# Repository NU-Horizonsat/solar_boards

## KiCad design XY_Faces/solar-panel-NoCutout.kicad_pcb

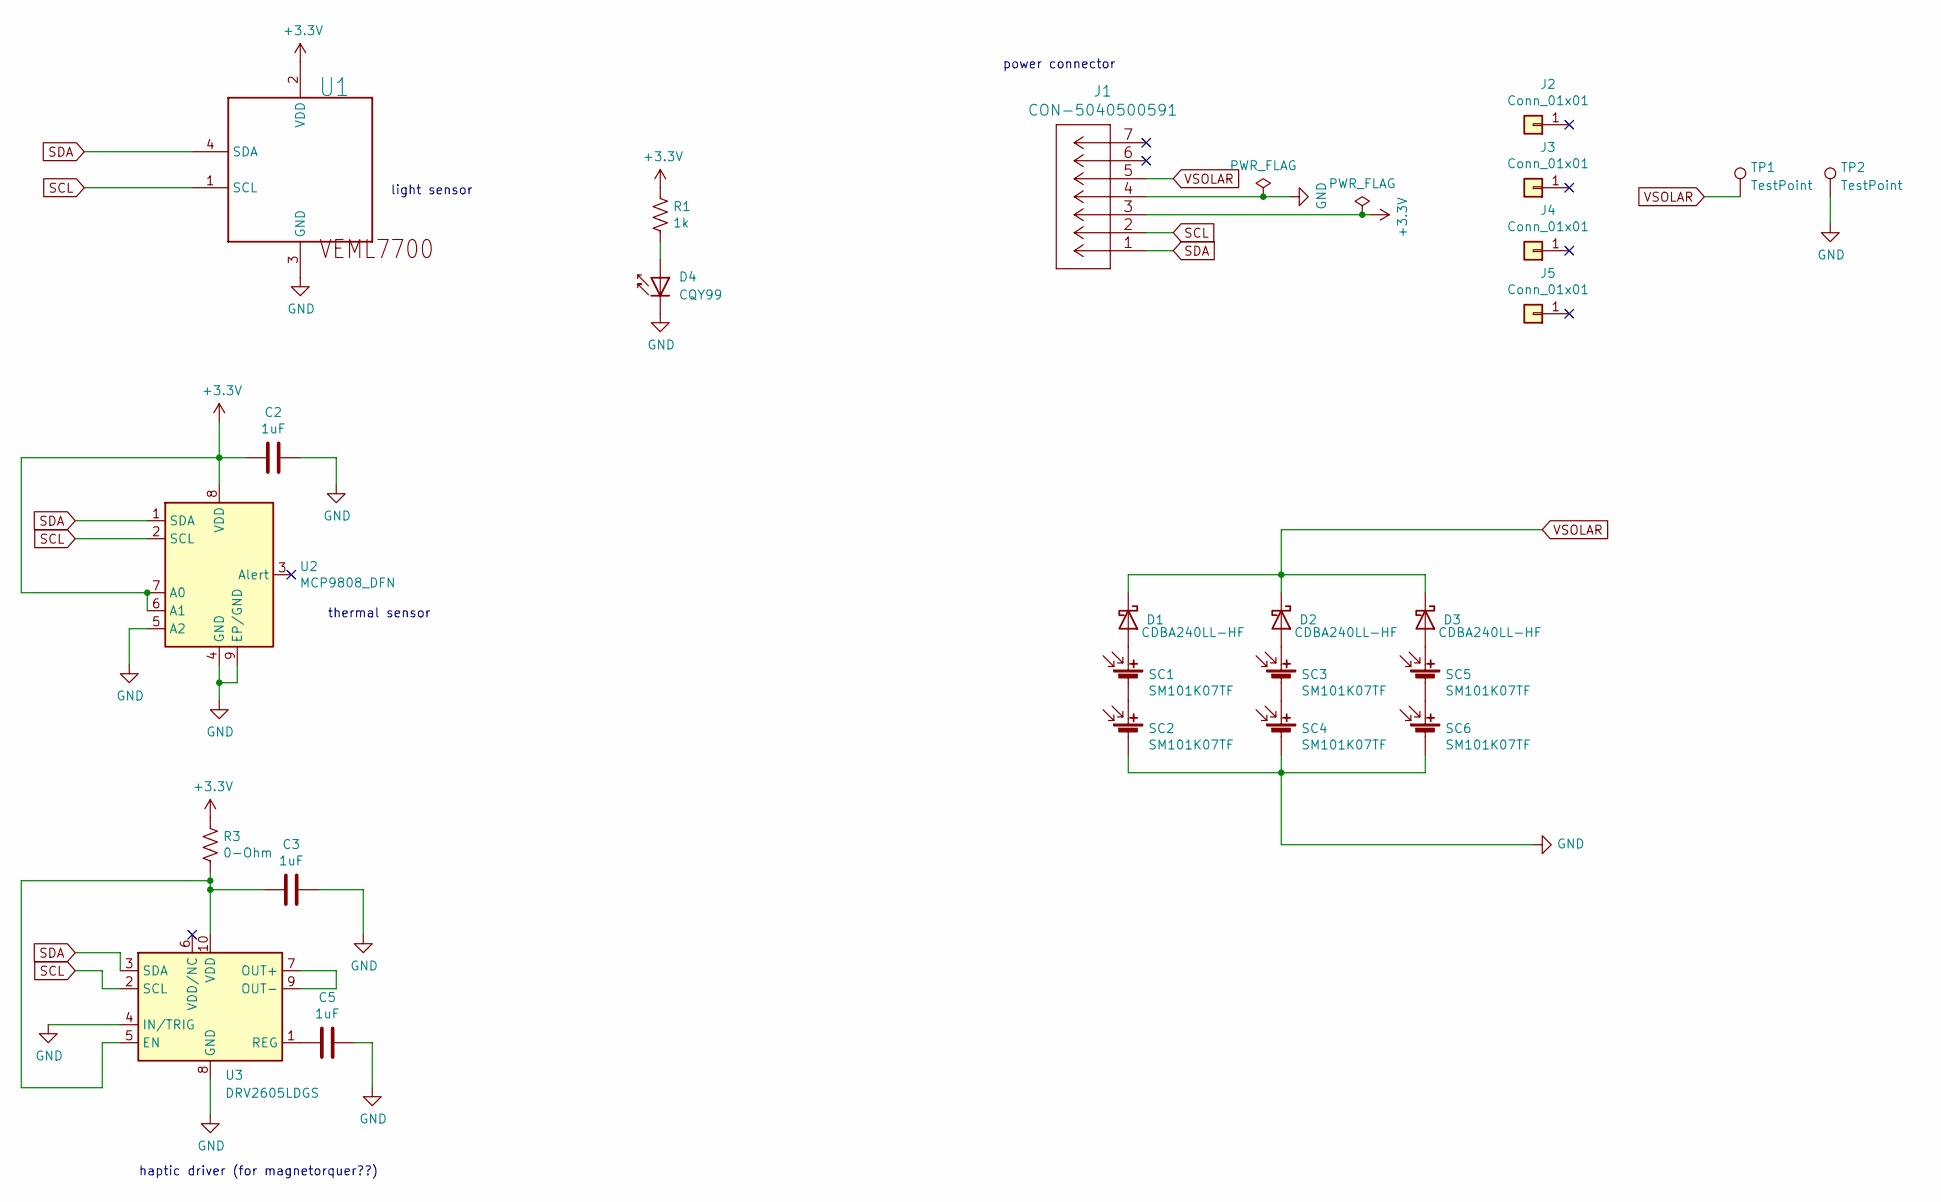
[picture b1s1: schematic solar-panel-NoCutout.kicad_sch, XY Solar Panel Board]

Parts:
C2, C3, C5: 1uF; C_0805_2012Metric
D1, D2, D3: CDBA240LL-HF; DO-214AC
D4: CQY99; LED_0603_1608Metric
J1: CON-5040500591; CON_5040500591
J2, J3, J4, J5: Conn_01x01; MountingHoles
R1: 1k; R_0603_1608Metric
R3: 0-Ohm; R_0603_1608Metric
SC1, SC2, SC3, SC4, SC5, SC6: SM101K07TF; KXOB101K08F-TR
TP1, TP2: TestPoint; Test Pad
U1: VEML7700; XDCR_VEML7700-TT
U2: MCP9808_DFN; MCP9808-NoLeadPackage
U3: DRV2605LDGS; VSSOP-10_3x3mm_P0.5mm

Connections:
+3V3: C2.1, J1.3, R1.1, R3.1, U1.2 (VDD), U2.6 (A1), U2.7 (A0), U2.8 (VDD)
GND: C2.2, C3.2, C5.2, D4.1 (K), J1.4, SC2.2 (-), SC4.2 (-), SC6.2 (-), TP2.1, U1.3 (GND), U2.4 (GND), U2.5 (A2), U2.9 (EP/GND), U3.4 (IN/TRIG), U3.8 (GND)
unnamed: C3.1, R3.2, U3.5 (EN), U3.10 (VDD)
unnamed: C5.1, U3.1 (REG)
unnamed: D1.2 (A), SC1.1 (+)
unnamed: D2.2 (A), SC3.1 (+)
unnamed: D3.2 (A), SC5.1 (+)
unnamed: D4.2 (A), R1.2
unnamed: SC1.2 (-), SC2.1 (+)
unnamed: SC3.2 (-), SC4.1 (+)
unnamed: SC5.2 (-), SC6.1 (+)
unnamed: U3.7 (OUT+), U3.9 (OUT-)
SCL: J1.2, U1.1 (SCL), U2.2 (SCL), U3.2 (SCL)
SDA: J1.1, U1.4 (SDA), U2.1 (SDA), U3.3 (SDA)
VSOLAR: D1.1 (K), D2.1 (K), D3.1 (K), J1.5, TP1.1

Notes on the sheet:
light sensor
power connector
haptic driver (for magnetorquer??)
thermal sensor

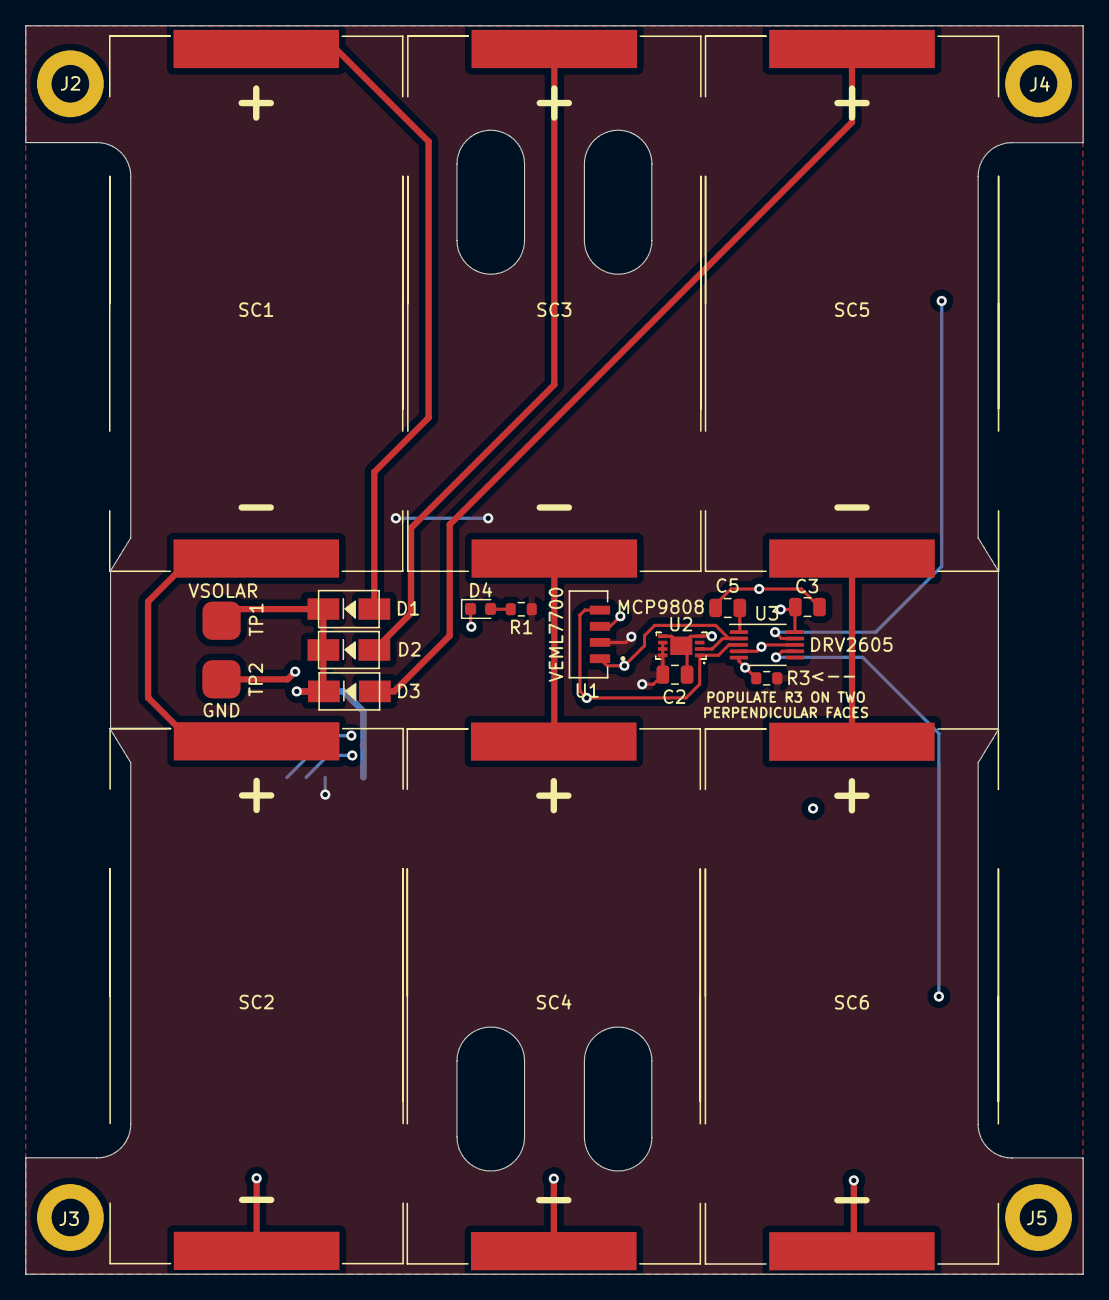
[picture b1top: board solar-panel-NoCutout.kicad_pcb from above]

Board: 4 copper layers, 83.0 x 98.0 mm, 25 parts (1 on the bottom side), 15 nets.

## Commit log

2023-12-28 moved copper routing
2024-01-24 removed coil wires, may have power conenctions that need to be removed and etc

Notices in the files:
parts and their libraries:
Copyright 2021 Accelerated Designs. All rights reserved.
